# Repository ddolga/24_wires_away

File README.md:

# 24 Wires Away

A small keyboard controller board (2 layers, ~29 × 57 mm) that drives a
full-size keyboard matrix over a single 24-wire connector: **16 rows + 8
columns = up to 128 keys**.

A Pro Micro–sized controller does not have enough free GPIO for a matrix
that size on its own, so the board expands its pins: 4 MCU pins are decoded
into 16 row lines, and 8 MCU pins read the 8 columns through a buffer.

The board is designed to work with both **5 V** controllers (Elite-C /
ATmega32U4) and **3.3 V** controllers with the same pinout (e.g. RP2040-based
boards like the Elite-Pi or SparkFun Pro Micro RP2040).

## Voltage compatibility

The matrix itself always runs at 5 V (`VBUS`). Each side of it is designed
to tolerate either MCU voltage:

- **Rows (MCU → matrix):** the 74HCT138 decoders run from `VBUS`. HCT inputs
  read anything above 2.0 V as high, so they accept both 3.3 V and 5 V logic.
  Their 5 V outputs only go to the matrix, never back to the MCU.
- **Columns (matrix → MCU):** the 74LVC245 runs from the MCU's own `VCC`, so
  its outputs follow the controller's voltage. Its inputs tolerate 5 V at
  either supply voltage.

**Requirement:** the controller's pin 24 must provide 5 V from USB (`VBUS`),
because that pin powers the decoders and pull-ups. This is true for the
Elite-C and RP2040 Pro Micro–style boards. On a nice!nano, pin 24 is the
battery input, so the board would get no 5 V there.

## Main ICs

### U1 — Pro Micro–compatible controller (Elite-C in the schematic)
Keebio's Elite-C: a Pro Micro–compatible module with USB-C, built around the
Microchip **ATmega32U4**, an 8-bit AVR running at 5 V / 16 MHz with native
USB. It runs the keyboard firmware (e.g. QMK) and shows up on the host as a
USB HID keyboard. It also powers the rest of the board from USB (`VBUS`).
3.3 V boards with the same pinout fit the same footprint.

### U3, U4 — 74HCT138 (3-to-8 line decoder/demultiplexer)
Each '138 takes a 3-bit address and pulls exactly one of its 8 outputs low
(outputs are active-low). The two chips are cascaded into a **4-to-16
decoder** that drives the 16 matrix rows:

- `PD1`, `PD0`, `PD4` → address inputs `A0`–`A2` on both chips
- `PC6` → acts as the 4th address bit: it goes to U3's active-low enable
  (`E0`) and U4's active-high enable (`E2`), so `PC6 = 0` selects U3
  (rows 1–8) and `PC6 = 1` selects U4 (rows 9–16)

The firmware scans the matrix by selecting one row at a time (driving it
low) and reading the columns: a column reading low means the key at that
row/column is pressed.

### U2 — 74LVC245APW (octal bus transceiver, used as a one-way buffer)
Sits between the 8 matrix columns (B side) and 8 MCU pins (A side).
`DIR` is tied low (data flows B → A, matrix → MCU), and `OE` is tied low
(always enabled). It is powered from the MCU's `VCC`, which is what makes the
column side work at 3.3 V or 5 V. In the schematic it uses KiCad's `74HC245`
symbol, which has the same pinout.

| Net | J1 pin | 74LVC245 | MCU pin |
|-----|--------|----------|---------|
| COL1 | 24 | B0 → A0 | PF4 (A3) |
| COL2 | 23 | B1 → A1 | PF5 (A2) |
| COL3 | 22 | B2 → A2 | PF6 (A1) |
| COL4 | 21 | B3 → A3 | PF7 (A0) |
| COL5 | 20 | B4 → A4 | PB1 (15) |
| COL6 | 19 | B5 → A5 | PB3 (14) |
| COL7 | 18 | B6 → A6 | PB2 (16) |
| COL8 | 17 | B7 → A7 | PB6 (10) |

## Passives

- **RN1, RN2** — 2 × 4-resistor 10 kΩ arrays (`R_Array_Convex_4x0603`) that
  pull `COL1`–`COL8` up to `VBUS`. They're required because the 74LVC245's
  inputs must not float, and the MCU's internal pull-ups can't reach the
  matrix through the buffer.
- **C1–C3** — 100 nF 0603 decoupling capacitors: C1 for U2 (`VCC`), C2 for
  U3 and C3 for U4 (`VBUS`). On the PCB, place each one next to its chip's
  supply pin.

## Connectors

- **J1** — JST PHD 2×12 (2.00 mm), the 24-wire keyboard matrix connector.
  Pins 1–16 are the rows (decoder outputs, U3 `Y0–Y7` then U4 `Y0–Y7`), and pins
  17–24 are the columns (`COL8`–`COL1`, through U2).
- **J3** — 6 solder-wire pads: `VBUS`, `GND`, and 4 spare MCU pins
  (`PD7`, `PE6`, `PB4`, `PB5`). Their purpose isn't labeled in the schematic.
  They might be meant for lock LEDs or other extras.

Unused controller pins: `TX0/PD3`, `RX1/PD2`, `RST`, and the extra Elite-C
pads `B7`, `D5`, `C7`, `F0`, `F1`.

## Status / to-do

- **PCB is out of date.** The schematic was changed (TXS0108E → 74LVC245,
  plus RN1, RN2 and C1–C3), but the board hasn't been updated yet. Run
  *Update PCB from Schematic*, reroute U2 (same TSSOP-20 footprint, different
  pinout), and place the new parts.
- **Firmware:** columns are active-low with external pull-ups, so don't
  enable the MCU's internal pull-ups on the column pins. They're harmless,
  but they do nothing here.
- **Ghosting:** with 16 × 8 lines and no diodes on this board, pressing
  several keys at once can cause ghosting unless the keyboard matrix itself
  has diodes.

## History

- **Oct 2026:** replaced the TXS0108E level translator with a 74LVC245. The
  TXS0108E's A side is limited to 3.6 V, so it couldn't run from a 5 V
  controller, and its `OE` pin was tied to GND, which disabled it. Added
  column pull-ups and decoupling capacitors.

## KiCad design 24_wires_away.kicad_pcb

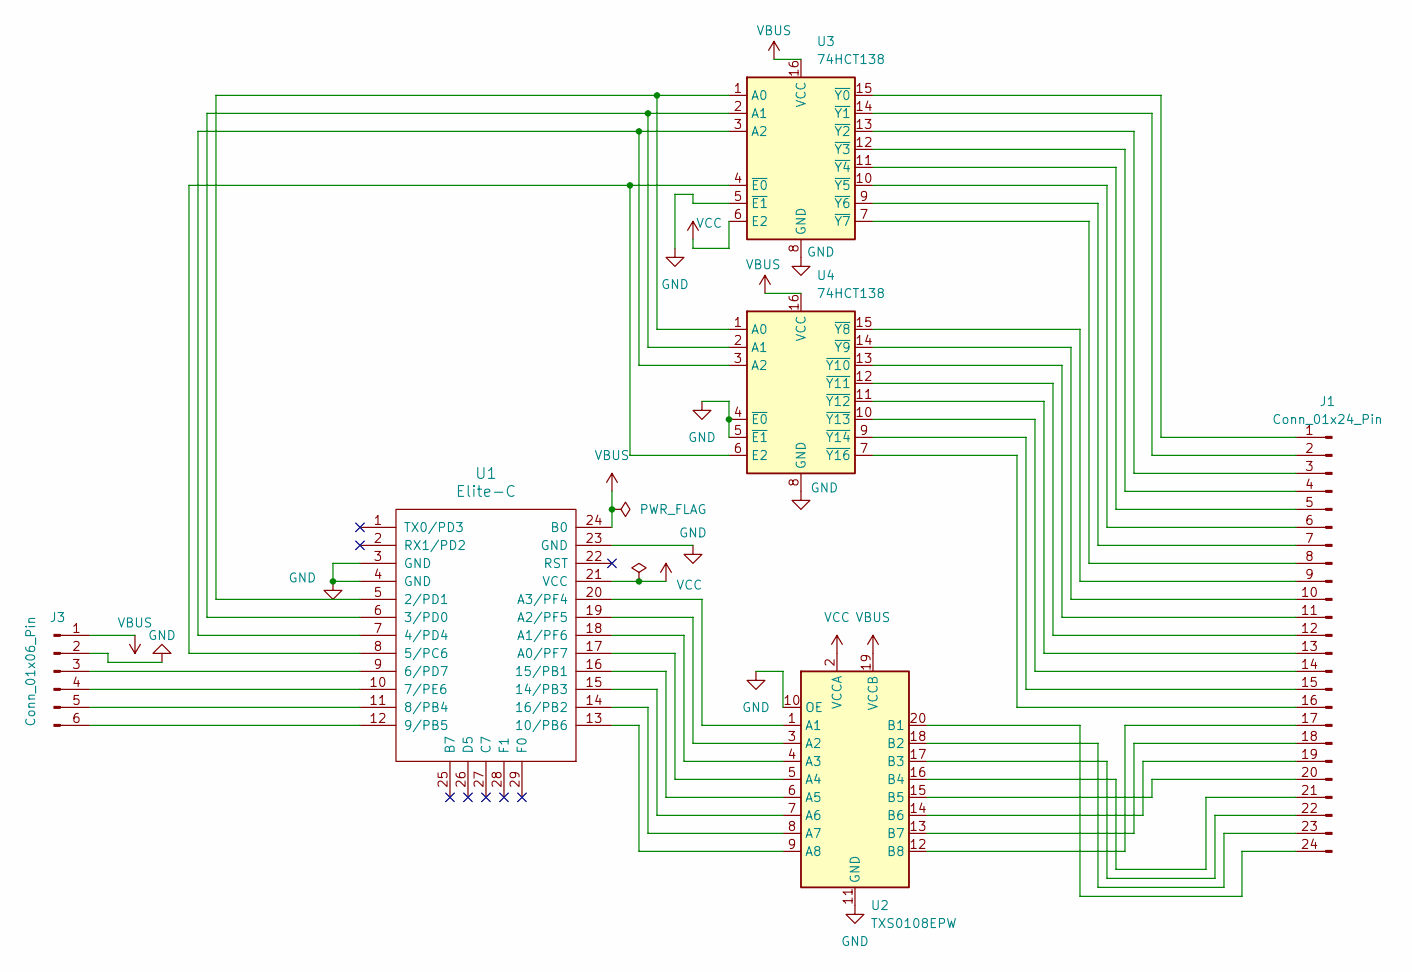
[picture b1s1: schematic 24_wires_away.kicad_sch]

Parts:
J1: Conn_01x24_Pin; JST_PHD_S24B-PHDSS_2x12_P2.00mm_Horizontal
J3: Conn_01x06_Pin; SolderWire-SMD-0.127sqmm_1x06_P3.7mm_D0.48mm_OD1mm
U1: Elite-C; Elite-C-castellated-24pin-holes
U2: TXS0108EPW; TSSOP-20_4.4x6.5mm_P0.65mm
U3, U4: 74HCT138; TSSOP-16_4.4x5mm_P0.65mm

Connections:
GND: J3.2, U1.3 (GND), U1.4 (GND), U1.23 (GND), U2.10 (OE), U2.11 (GND), U3.5 (~E1), U3.8 (GND), U4.4 (~E0), U4.5 (~E1), U4.8 (GND)
unnamed: J1.1, U3.15 (~Y0)
unnamed: J1.2, U3.14 (~Y1)
unnamed: J1.3, U3.13 (~Y2)
unnamed: J1.4, U3.12 (~Y3)
unnamed: J1.5, U3.11 (~Y4)
unnamed: J1.6, U3.10 (~Y5)
unnamed: J1.7, U3.9 (~Y6)
unnamed: J1.8, U3.7 (~Y7)
unnamed: J1.9, U4.15 (~Y8)
unnamed: J1.10, U4.14 (~Y9)
unnamed: J1.11, U4.13 (~Y10)
unnamed: J1.12, U4.12 (~Y11)
unnamed: J1.13, U4.11 (~Y12)
unnamed: J1.14, U4.10 (~Y13)
unnamed: J1.15, U4.9 (~Y14)
unnamed: J1.16, U4.7 (~Y16)
unnamed: J1.17, U2.12 (B8)
unnamed: J1.18, U2.13 (B7)
unnamed: J1.19, U2.14 (B6)
unnamed: J1.20, U2.15 (B5)
unnamed: J1.21, U2.16 (B4)
unnamed: J1.22, U2.17 (B3)
unnamed: J1.23, U2.18 (B2)
unnamed: J1.24, U2.20 (B1)
unnamed: J3.3, U1.9 (6/PD7)
unnamed: J3.4, U1.10 (7/PE6)
unnamed: J3.5, U1.11 (8/PB4)
unnamed: J3.6, U1.12 (9/PB5)
unnamed: U1.5 (2/PD1), U3.1 (A0), U4.1 (A0)
unnamed: U1.6 (3/PD0), U3.2 (A1), U4.2 (A1)
unnamed: U1.7 (4/PD4), U3.3 (A2), U4.3 (A2)
unnamed: U1.8 (5/PC6), U3.4 (~E0), U4.6 (E2)
unnamed: U1.13 (10/PB6), U2.9 (A8)
unnamed: U1.15 (14/PB3), U2.7 (A6)
unnamed: U1.16 (15/PB1), U2.6 (A5)
unnamed: U1.14 (16/PB2), U2.8 (A7)
unnamed: U1.17 (A0/PF7), U2.5 (A4)
unnamed: U1.18 (A1/PF6), U2.4 (A3)
unnamed: U1.19 (A2/PF5), U2.3 (A2)
unnamed: U1.20 (A3/PF4), U2.1 (A1)
VBUS: J3.1, U1.24 (B0), U2.19 (VCCB), U3.16 (VCC), U4.16 (VCC)
VCC: U1.21 (VCC), U2.2 (VCCA), U3.6 (E2)

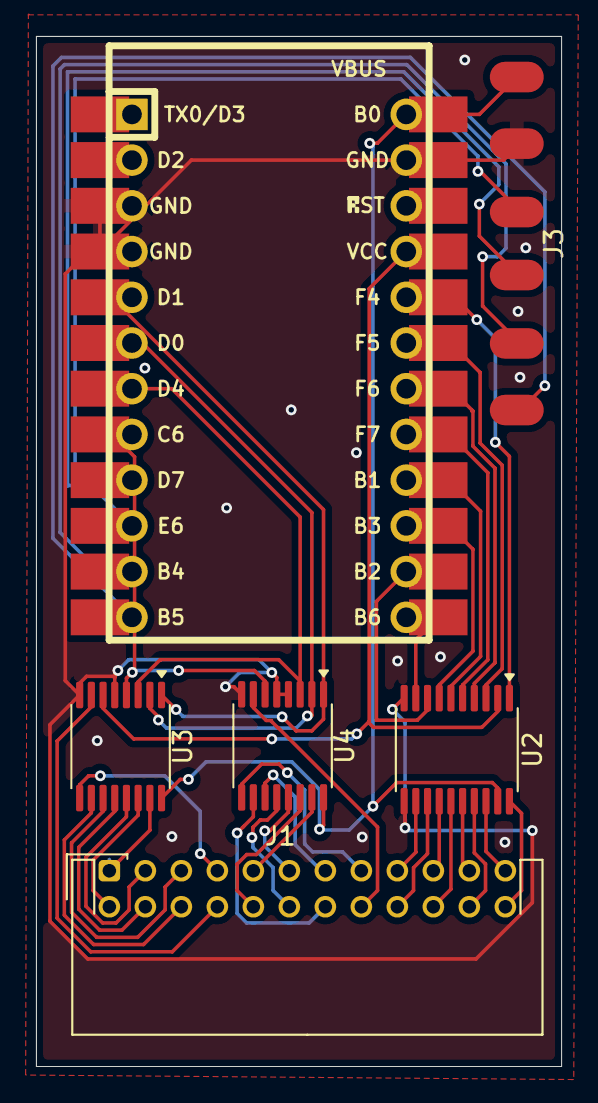
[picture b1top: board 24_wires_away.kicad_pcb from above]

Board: 2 copper layers, 29.2 x 57.2 mm, 6 parts (0 on the bottom side), 43 nets.

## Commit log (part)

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2026-04-27 more changes
